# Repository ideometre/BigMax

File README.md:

# [Bienvenue sur le répertoire du projet](https://maxime-hanicotte.github.io/BigMax/)

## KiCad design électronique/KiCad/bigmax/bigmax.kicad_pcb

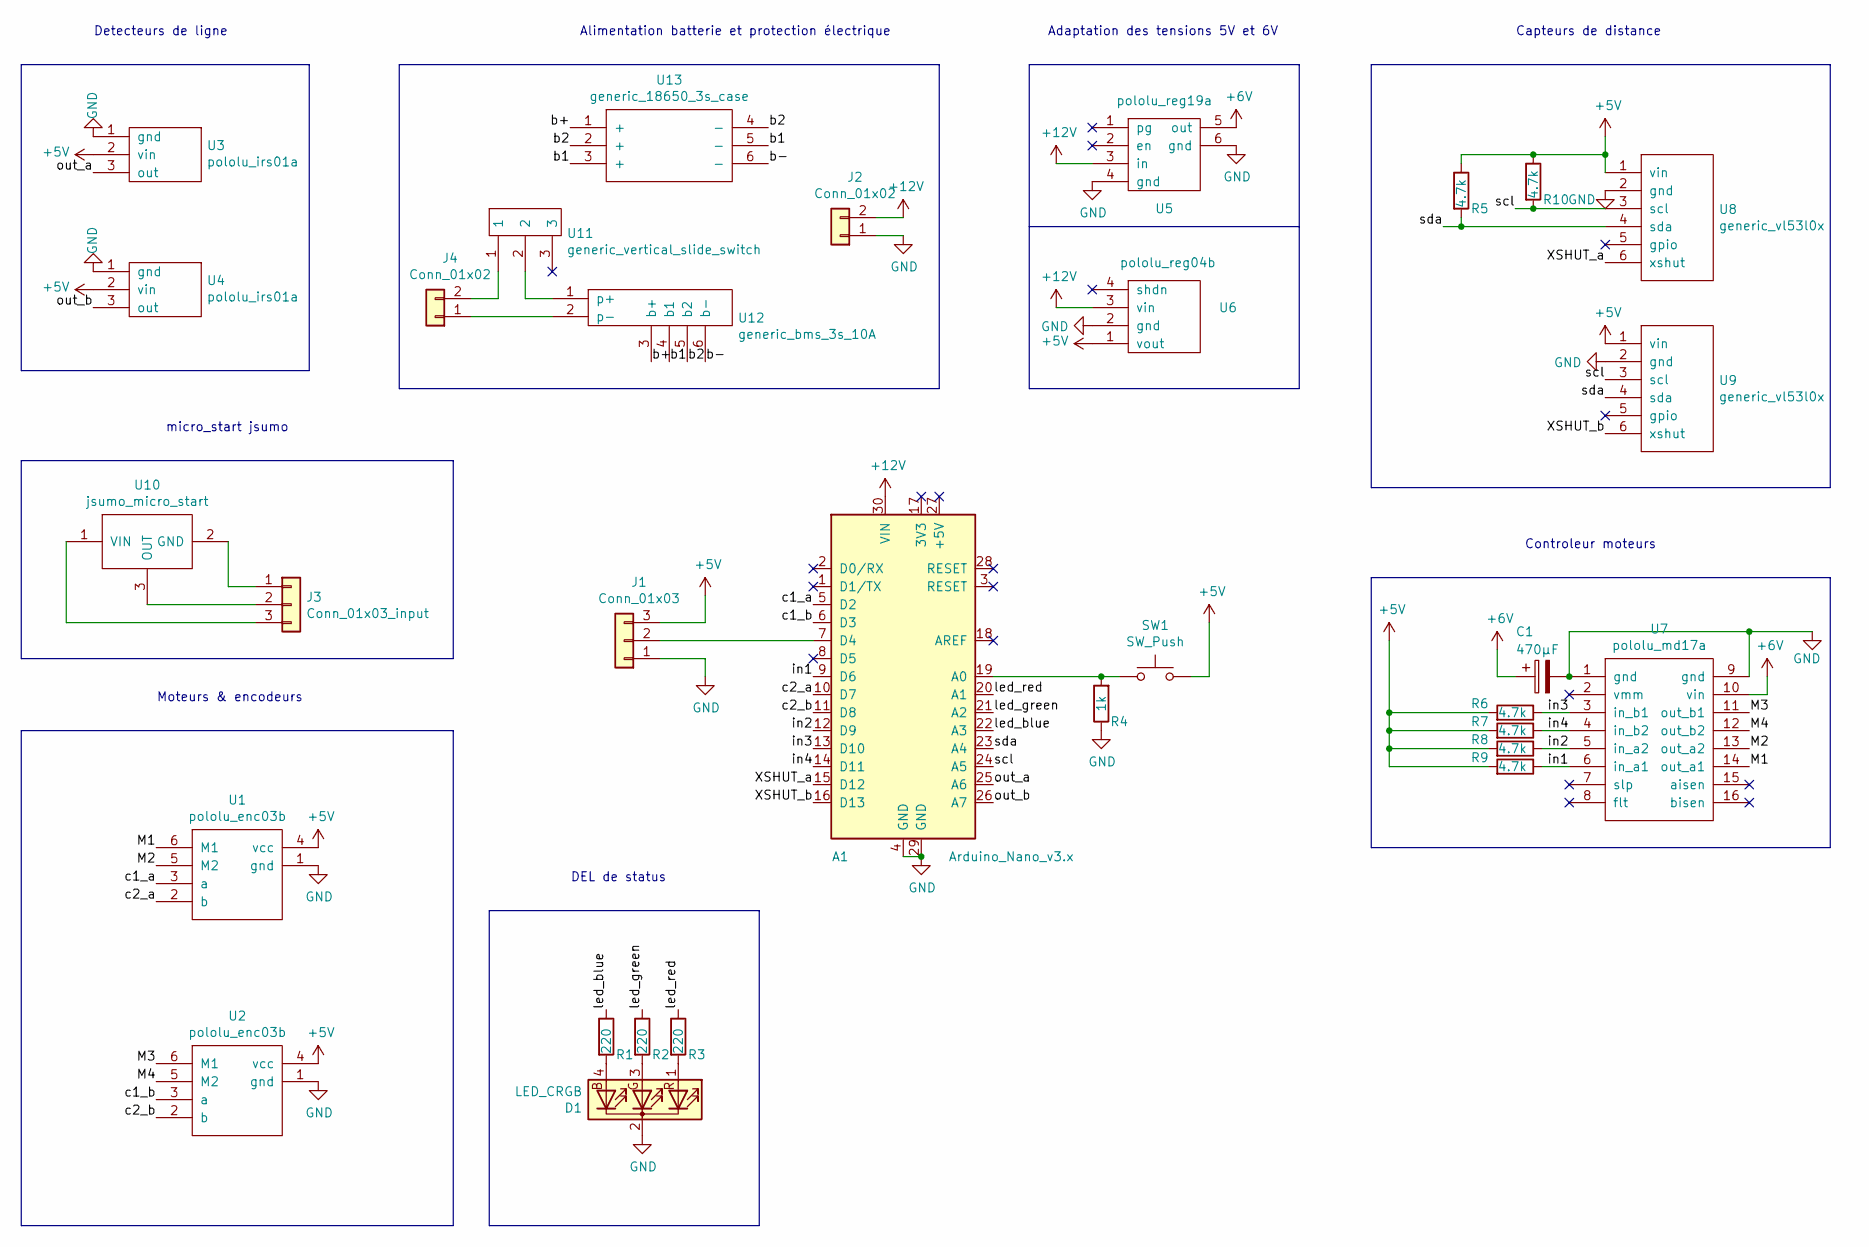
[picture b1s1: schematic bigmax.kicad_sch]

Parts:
A1: Arduino_Nano_v3.x; Arduino_Nano
C1: 470µF; CP_Radial_D10.0mm_P5.00mm
D1: LED_CRGB; LED_D5.0mm-4
J1: Conn_01x03; Pin_Header_Angled_1x03_Pitch2.54mm
J2, J4: Conn_01x02; Pin_Header_Angled_1x02_Pitch2.54mm
J3: Conn_01x03_input; Pin_Header_Angled_1x03_Pitch2.54mm
R1, R2, R3: 220; R_Axial_DIN0207_L6.3mm_D2.5mm_P10.16mm_Horizontal
R4: 1k; R_Axial_DIN0207_L6.3mm_D2.5mm_P10.16mm_Horizontal
R5, R6, R7, R8, R9, R10: 4.7k; R_Axial_DIN0207_L6.3mm_D2.5mm_P10.16mm_Horizontal
SW1: SW_Push; SW_PUSH_6mm
U1, U2: pololu_enc03b
U3, U4: pololu_irs01a
U5: pololu_reg19a
U6: pololu_reg04b
U7: pololu_md17a
U8, U9: generic_vl53l0x
U10: jsumo_micro_start
U11: generic_vertical_slide_switch; Pin_Header_Straight_1x03_Pitch2.54mm
U12: generic_bms_3s_10A
U13: generic_18650_3s_case; CB-18650-PC6

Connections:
+5V: J1.3, R5.1, R6.2, R7.2, R8.2, R9.2, R10.1, SW1.2, U1.4 (vcc), U2.4 (vcc), U3.2 (vin), U4.2 (vin), U6.1 (vout), U8.1 (vin), U9.1 (vin)
+6V: C1.1, U5.5 (out), U7.10 (vin)
+12V: A1.30 (VIN), J2.2, U5.3 (in), U6.3 (vin)
/M1: U1.6 (M1), U7.14 (out_a1)
/M2: U1.5 (M2), U7.13 (out_a2)
/M3: U2.6 (M1), U7.11 (out_b1)
/M4: U2.5 (M2), U7.12 (out_b2)
/XSHUT_a: A1.15 (D12), U8.6 (xshut)
/XSHUT_b: A1.16 (D13), U9.6 (xshut)
/b1: U12.4 (b1), U13.3 (+), U13.5 (-)
/b2: U12.5 (b2), U13.2 (+), U13.4 (-)
/b+: U12.3 (b+), U13.1 (+)
/b-: U12.6 (b-), U13.6 (-)
/c1_a: A1.5 (D2), U1.3 (a)
/c1_b: A1.6 (D3), U2.3 (a)
/c2_a: A1.10 (D7), U1.2 (b)
/c2_b: A1.11 (D8), U2.2 (b)
/in1: A1.9 (D6), R9.1, U7.6 (in_a1)
/in2: A1.12 (D9), R8.1, U7.5 (in_a2)
/in3: A1.13 (D10), R6.1, U7.3 (in_b1)
/in4: A1.14 (D11), R7.1, U7.4 (in_b2)
/led_blue: A1.22 (A3), R1.1
/led_green: A1.21 (A2), R2.1
/led_red: A1.20 (A1), R3.1
/out_a: A1.25 (A6), U3.3 (out)
/out_b: A1.26 (A7), U4.3 (out)
/scl: A1.24 (A5), R10.2, U8.3 (scl), U9.3 (scl)
/sda: A1.23 (A4), R5.2, U8.4 (sda), U9.4 (sda)
GND: A1.4 (GND), A1.29 (GND), C1.2, D1.2 (K), J1.1, J2.1, R4.1, U1.1 (gnd), U2.1 (gnd), U3.1 (gnd), U4.1 (gnd), U5.4 (gnd), U5.6 (gnd), U6.2 (gnd), U7.1 (gnd), U7.9 (gnd), U8.2 (gnd), U9.2 (gnd)
unnamed: A1.7 (D4), J1.2
unnamed: A1.19 (A0), R4.2, SW1.1
unnamed: D1.1 (RA), R3.2
unnamed: D1.3 (GA), R2.2
unnamed: D1.4 (BA), R1.2
unnamed: J3.1, U10.2 (GND)
unnamed: J3.2, U10.3 (OUT)
unnamed: J3.3, U10.1 (VIN)
unnamed: J4.1, U12.2 (p-)
unnamed: J4.2, U11.1
unnamed: U11.2, U12.1 (p+)

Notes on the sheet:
Moteurs & encodeurs
Alimentation batterie et protection électrique
Controleur moteurs
Adaptation des tensions 5V et 6V
DEL de status
Capteurs de distance
micro_start jsumo
Detecteurs de ligne

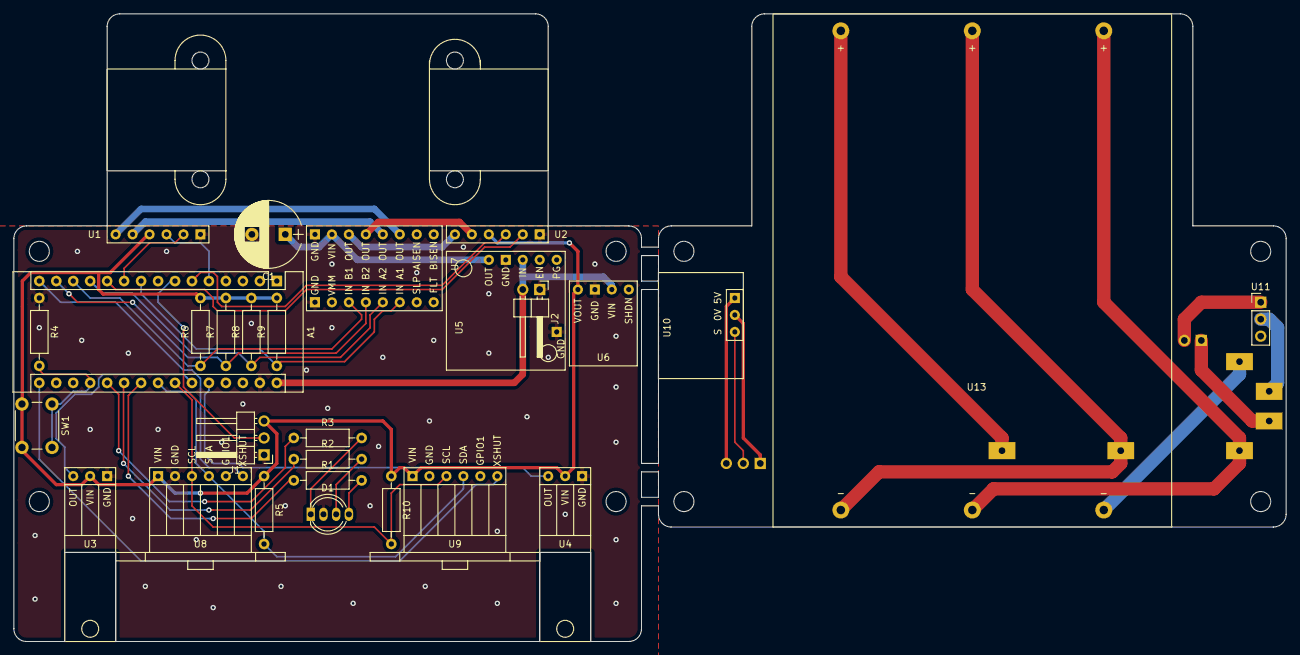
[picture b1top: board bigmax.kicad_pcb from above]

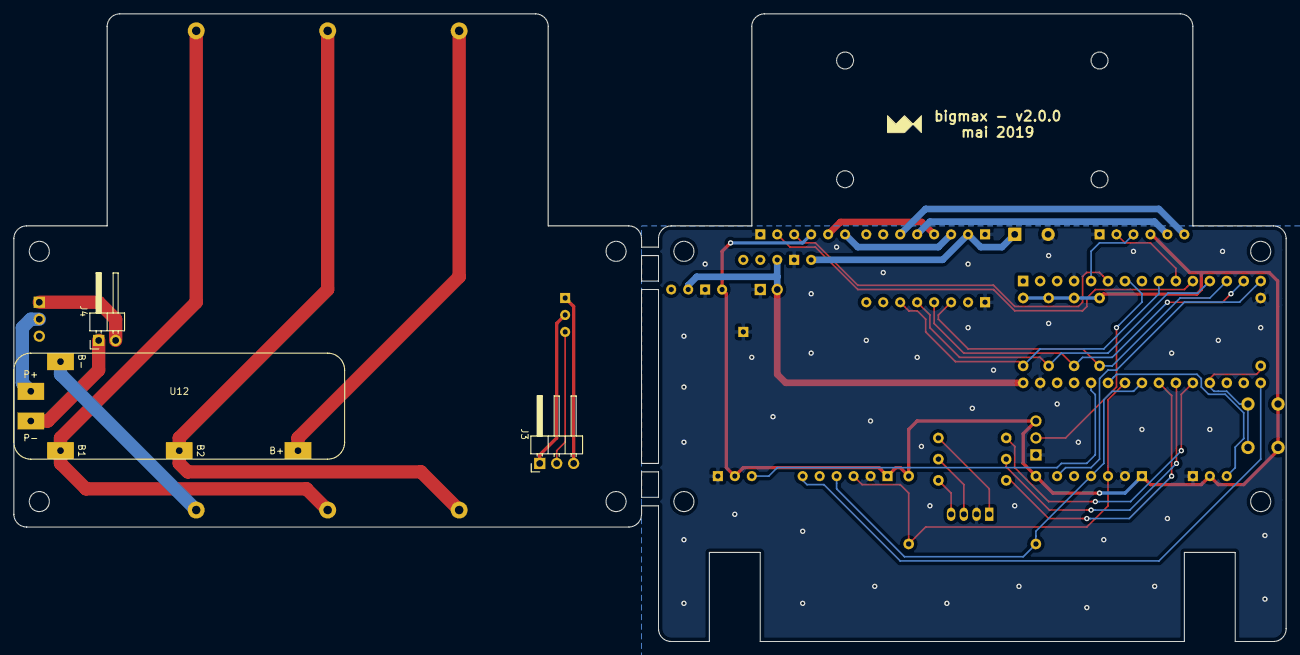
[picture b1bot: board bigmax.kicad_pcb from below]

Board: 2 copper layers, 190.5 x 94.0 mm, 31 parts (3 on the bottom side), 40 nets.

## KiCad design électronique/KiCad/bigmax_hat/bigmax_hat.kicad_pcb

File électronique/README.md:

Ce dossier contient les élements liés au développement électronique

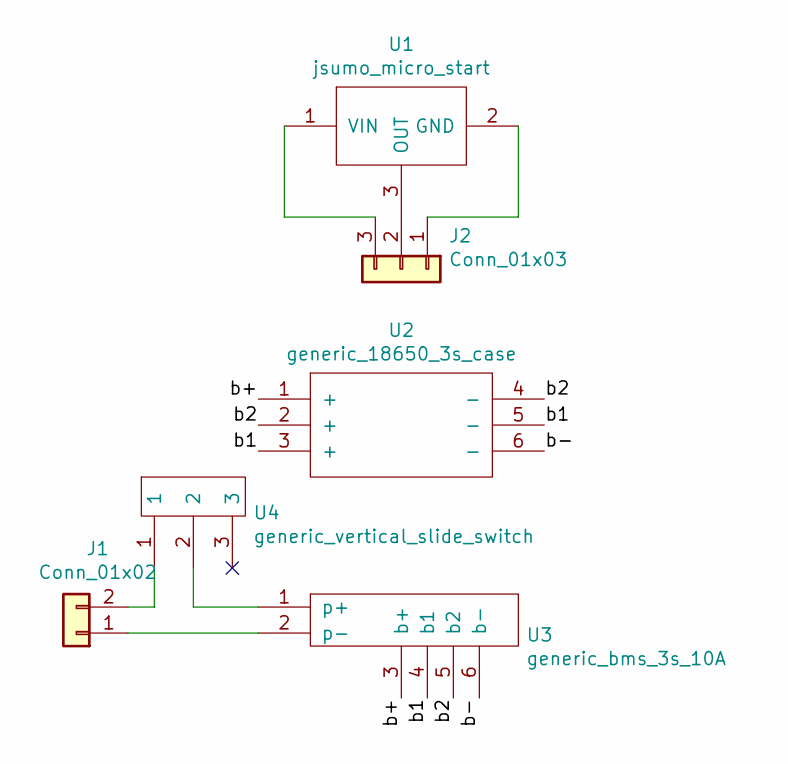
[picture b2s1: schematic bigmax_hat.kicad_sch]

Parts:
J1: Conn_01x02; Pin_Header_Angled_1x02_Pitch2.54mm
J2: Conn_01x03; Pin_Header_Angled_1x03_Pitch2.54mm
U1: jsumo_micro_start
U2: generic_18650_3s_case; CB-18650-PC6
U3: generic_bms_3s_10A
U4: generic_vertical_slide_switch; Pin_Header_Straight_1x03_Pitch2.54mm

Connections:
/b1: U2.3 (+), U2.5 (-), U3.4 (b1)
/b2: U2.2 (+), U2.4 (-), U3.5 (b2)
/b+: U2.1 (+), U3.3 (b+)
/b-: U2.6 (-), U3.6 (b-)
unnamed: J1.1, U3.2 (p-)
unnamed: J1.2, U4.1
unnamed: J2.1, U1.2 (GND)
unnamed: J2.2, U1.3 (OUT)
unnamed: J2.3, U1.1 (VIN)
unnamed: U3.1 (p+), U4.2

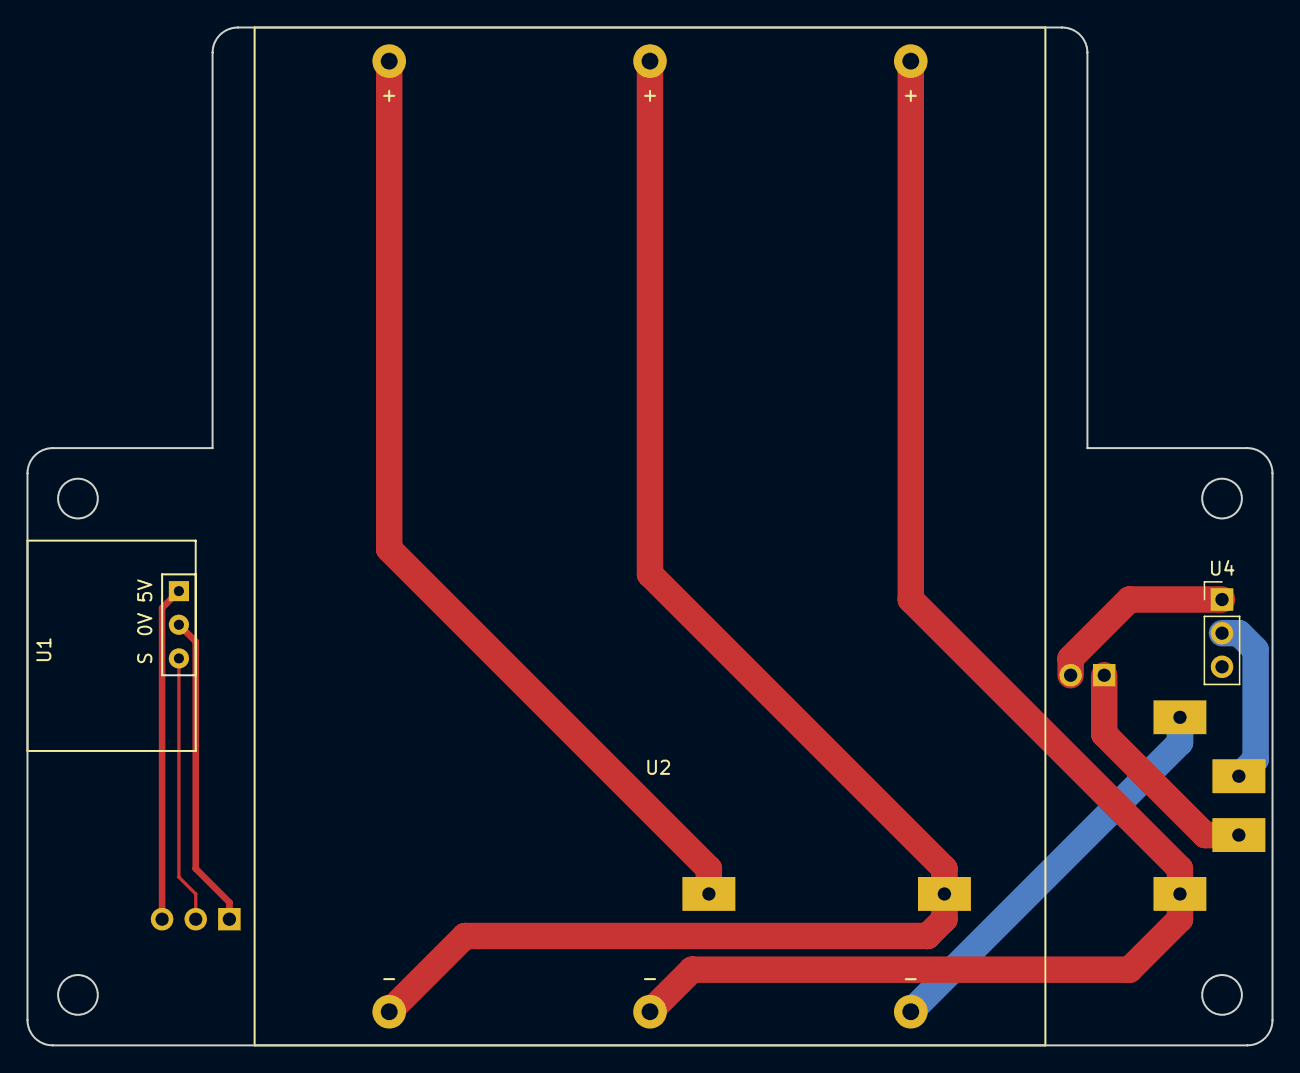
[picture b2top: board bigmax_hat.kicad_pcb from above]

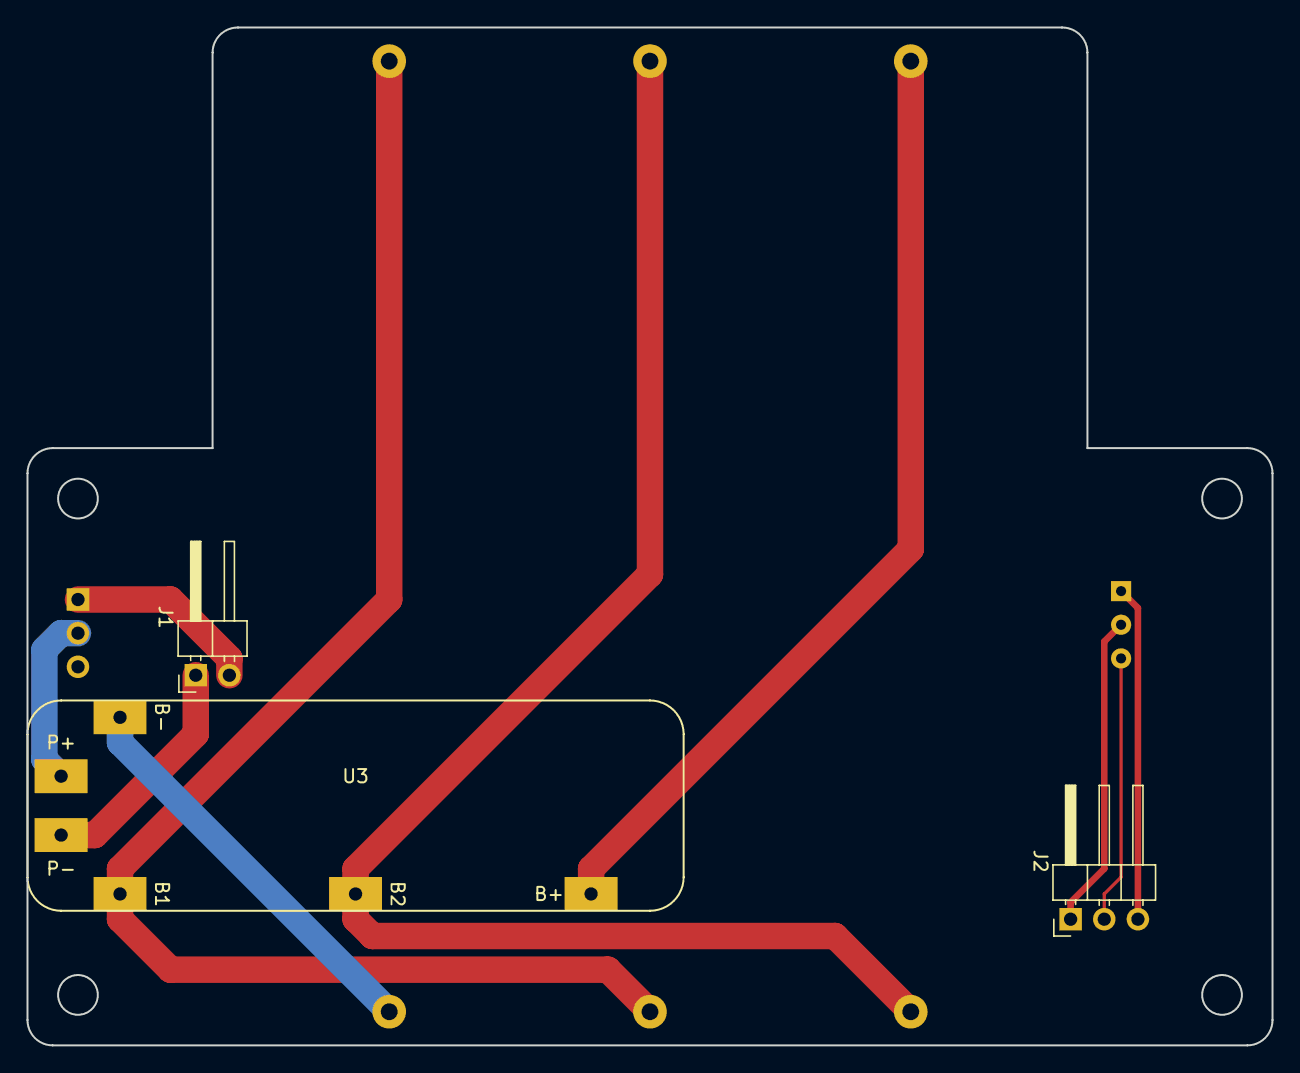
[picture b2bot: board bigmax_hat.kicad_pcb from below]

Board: 2 copper layers, 94.0 x 76.8 mm, 6 parts (3 on the bottom side), 10 nets.

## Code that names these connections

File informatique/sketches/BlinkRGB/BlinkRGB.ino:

/*
  Blink rgb with a state machine strategy
*/
#define LED_RED A1
#define LED_GREEN A2
#define LED_BLUE A3
#define PUSH_BUTTON 4
#define OFF 0
#define RED 1
#define GREEN 2
#define BLUE 3

boolean RGB_CHANGE = false;
int RGB_STATE = 0;
int last_btn = 0;
int btn = 0;

// the setup function runs once when you press reset or power the board
void setup() {
  setup_serial();
  setup_btn();
  setup_rgb();
}

// the loop function runs over and over again forever
void loop() {
  // read sensors
  //read_btn();
  RGB_CHANGE = true;
  // apply state
  if(RGB_CHANGE){
    write_rgb();
  }
  // wait for a second
  delay(1000);
}

// the loop function runs over and over again forever
void read_btn() {
  btn = digitalRead(PUSH_BUTTON);
  Serial.print(last_btn);
  Serial.print("   ");
  Serial.println(btn);
  if(!last_btn && !btn){ // because mode pullup
    RGB_CHANGE = true;
    last_btn = 1;
  }
  else if(last_btn && btn){
    last_btn = 0;
  }
}

// the loop function runs over and over again forever
void write_rgb() {
  switch(RGB_STATE){
    case OFF :
      digitalWrite(LED_RED, HIGH);  // turn the LED on (HIGH is the voltage level)
      digitalWrite(LED_BLUE, LOW);  // turn the LED off by making the voltage LOW
      digitalWrite(LED_GREEN, LOW); // turn the LED off by making the voltage LOW
      Serial.println("RED");
      RGB_STATE = RED;
      break;

    case RED :
      digitalWrite(LED_RED, LOW);   // turn the LED off by making the voltage LOW
      digitalWrite(LED_BLUE, LOW);  // turn the LED off by making the voltage LOW
      digitalWrite(LED_GREEN, HIGH);// turn the LED on (HIGH is the voltage level)
      Serial.println("GREEN");
      RGB_STATE = GREEN;
      break;
      
    case GREEN :
      digitalWrite(LED_RED, LOW);   // turn the LED off by making the voltage LOW
      digitalWrite(LED_BLUE, HIGH); // turn the LED on (HIGH is the voltage level)
      digitalWrite(LED_GREEN, LOW); // turn the LED off by making the voltage LOW
      Serial.println("BLUE");
      RGB_STATE = BLUE;
      break;
      
    default :  
      digitalWrite(LED_RED, LOW);  // turn the LED off by making the voltage LOW
      digitalWrite(LED_BLUE, LOW); // turn the LED off by making the voltage LOW
      digitalWrite(LED_GREEN, LOW);// turn the LED on (HIGH is the voltage level)
      Serial.println("OFF");
      RGB_STATE = OFF;
      break;     
  }
  RGB_CHANGE = false;
}

void setup_serial() {
  // initialize serial
  Serial.begin(115200);
}

void setup_rgb() {
  // initialize pins as outputs
  pinMode(LED_RED, OUTPUT);
  pinMode(LED_BLUE, OUTPUT);
  pinMode(LED_GREEN, OUTPUT);
}

void setup_btn() {
  // initialize push btn
  pinMode(PUSH_BUTTON, INPUT_PULLUP);
}

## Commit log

2018-04-13 Set theme jekyll-theme-slate
2018-04-13 Set theme jekyll-theme-minimal
2018-04-13 minor change with headers
2018-04-17 ajout des dossiers et fichiers README.md
2018-04-17 modification de la page web du projet. modification du README.md du répertoire source
2018-04-17 suppression du fichier ./_config.yml, theme du site
2018-04-17 ajout des titres pour la page web
2018-04-17 ajout des liens vers les sous-répertoires sur la page web
2018-04-17 ajout des détails pour la partie électronique
2018-04-17 modification des détails pour la partie électronique de la page web
2018-04-17 modification des liens sur les sous-titres de la page web
2018-04-17 ajout des détails dans les parties mécanique, électrique et informatique
2018-04-17 ajout d'un lien vers la page web dans ./README.md
2018-04-17 modification du titre de la page
2018-04-17 modification du lien pour le sous-titre electronique
2018-04-19 ajout du projet Kicad des pièces 2D et des datasheets
2018-05-01 Ajout des fichiers readme.md dans les sous-dossiers
2018-05-09 modifications mineures
2018-05-16 Update issue templates
2018-06-16 ajout du dossier libraries
2018-06-16 ajout de nouveaux composants kicad
2018-06-16 ajout des logos sur la page
2018-06-16 modif des logos sur la page
2018-08-07 Update README.md
    correction des fautes
2018-11-27 Create LICENSE
2018-12-11 Modification sur le projet KiCad, ajout de parechoc, ajout de sketch_bigmax
2018-12-11 Suppression du projet Kicad
2018-12-12 coorection du merge sur le code arduino
2019-01-28 ajout de code source pour tests.
2019-01-31 mise à jour du projet kicad en ajoutant des résistances de pull-up sur la commande des moteurs et une capacité de découplage en entrée du controller moteurs
2019-02-16 Dernière mise à jour du pcb BigMax v1 avant commande ajout des pins pour MicroStart
2019-02-16 Ajout du dossier Sumobot Challenge 2017 dans docs
2019-02-16 Ajout des bibliotheques et des tests arduino pour BigMax v1
2019-05-15 Bigmax v2 - mai 2019
2019-05-24 add minis
2019-05-24 add electronic part symbols
2019-05-27 update logo
2019-05-27 Update logos
2019-05-27 update logos again
2019-08-16 ajout de la derniere version du code
2020-01-30 nettoyage du projet kicad
2022-02-02 first 22 push
2022-02-02 update mx link and _config settings
